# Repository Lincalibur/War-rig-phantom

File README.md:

<div align="center">

# War-rig-phantom
### *A Portable OPSEC/OSINT Recon Deck*

**A full ESP32-DIV multi-tool handheld (WiFi / BLE / 2.4 GHz / sub-GHz) plus standalone recon modules, with GPS-tagged logging**

**[Build page](https://lincalibur.github.io/War-rig-phantom/)**: boards, wiring diagram, parts checklist and build order

</div>

---

## Overview

**War-rig-phantom** is a portable wireless multi-tool and recon kit made of separate modules. Each module has its own screen and job:

- **`SPECTRE`** (role: `HUB`): the active handheld — an ESP32-WROOM-32U with a router antenna on U.FL, a **3.5" ILI9488 8-bit parallel TFT** and a NEO-7M GPS. It runs the ported **CyberDeck orchestrator** (a Ghost-ESP-style toolkit), driven from the `CONSOLE` phone app over BLE, on the ESP32's **built-in 2.4 GHz radio**: WiFi scan/deauth/evil-portal/packet-monitor/wardrive, BLE scan/spam, handshake → `.pcap` streamed to the phone, and HID. No radio shield, no buttons, no SD; one expansion SPI slot is reserved for a single future CC1101/NRF24.
- **`SENTINEL`** (roles: `WIFI-NODE` + `READOUT`): an ESP32-C3 WiFi/BLE sniffer streams over a one-way 19200 UART to an Arduino UNO with a 3.5" screen. It's the passive, always-on watcher — flags trackers, tails and attacks, and never transmits.
- **`BEACON`** (role: `STATUS`): a removable ESP32-C3 + OLED watch that logs GPS and WiFi scans to a phone.
- **`CONSOLE`:** the Android (Flutter) app that drives `SPECTRE` over BLE.

The modules share one 18650 pack and a 5 V boost module. Later, all the logs go to a laptop for analysis.

> **Scope & Ethics**
> `SPECTRE`'s orchestrator **includes active, transmitting tools** (WiFi deauth, beacon/probe/karma flood, evil portal, BLE spam, a best-effort BLE adv-flood "jammer", and HID) — all on the ESP32's built-in 2.4 GHz radio.
> - Use them **only** against hardware you own and control — the project's test laptop and spare router, on an isolated bench.
> - Never transmit against networks, devices or people you don't own. Deauth is illegal in most jurisdictions when aimed at others, and the radio interferes with anyone nearby.
> - The passive modules (`SENTINEL`, `BEACON`) only listen and log.
>
> This is an authorized-testing and learning platform. You are responsible for staying within the law.

## Architecture

```mermaid
flowchart TD
    subgraph SPECTREG["SPECTRE (HUB) · ported orchestrator firmware"]
      ESP["ESP32-WROOM-32U<br/>router antenna on U.FL<br/>built-in 2.4 GHz WiFi + BLE"]
      TFT["3.5 in ILI9488<br/>8-bit parallel, 320x480"]
      GPS["GPS · NEO-7M"]
      EXP["expansion SPI slot<br/>1 future radio, unused"]
      ESP -->|8-bit parallel| TFT
      GPS -->|UART2| ESP
      ESP -.->|SPI, future| EXP
    end
    CONSOLE["CONSOLE · Android app"] <-->|BLE| ESP
    ESP -.->|handshake .pcap over BLE| CONSOLE
    subgraph SENTG["SENTINEL (WIFI-NODE + READOUT) · passive, never TX"]
      WIFI["ESP32-C3<br/>promiscuous"] -->|UART 19200| READOUT["UNO + 3.5 in TFT"]
    end
    BEACON["BEACON (STATUS)<br/>C3 + OLED watch"] -->|CSV| PHONE["Android phone"]
    CONSOLE -.->|later| LAPTOP["Laptop analysis"]
    PHONE -.->|later| LAPTOP

    subgraph POWER["Power"]
      direction LR
      BAT["3x 18650 in parallel"] --> MSW["master switch"] --> BOOST["5V 2A charge/boost"] --> RAIL["5 V to every module"]
    end
```

SPECTRE wiring is documented in [`docs/hardware-layout.md`](docs/hardware-layout.md#spectre-pins) and [`hardware/spectre-pcb/PINOUT.md`](hardware/spectre-pcb/PINOUT.md). (The drawing [`docs/wiring.svg`](docs/wiring.svg) predates the 2026-11-15 pin remap and is stale.) Board names are defined in [`docs/hardware-layout.md`](docs/hardware-layout.md#module-names).

## Repository

| Path | What's in it |
|---|---|
| [`docs/OVERVIEW.md`](docs/OVERVIEW.md) | **Start here.** Goals, decisions, capabilities, status and next steps |
| [`docs/hardware-layout.md`](docs/hardware-layout.md) | The current build: board names, HUB pins, power, case |
| [`docs/case-planner.html`](docs/case-planner.html) | 3D case layout planner: size parts, drag them around the clamshell, check fit, export an OpenSCAD filler (live on the Pages site) |
| [`cad/wiring/`](cad/wiring/) | Script that draws the HUB wiring diagrams |
| [`docs/build-page.html`](docs/build-page.html) | Source of the build page (deployed by `.github/workflows/pages.yml`) |
| [`spectre/v1/`](spectre/v1/) | **SPECTRE firmware** — the orchestrator on one ESP32-WROOM-32U (see [`STATUS.md`](spectre/v1/STATUS.md)) |
| [`sentinel/v1/`](sentinel/v1/) | **SENTINEL firmware** — the passive watcher (ESP32-C3 + UNO pair) |
| [`hardware/spectre-pcb/`](hardware/spectre-pcb/) | SPECTRE custom carrier PCB (KiCad), on branch `spectre-pcb` |
| [`app/`](app/) | **CONSOLE** — the Android (Flutter) app that drives SPECTRE over BLE |
| [`docs/proto-readout-wiring.html`](docs/proto-readout-wiring.html) | SENTINEL C3 → UNO readout wiring |
| [`docs/BOARD-BLE-SCAN-ESP32-1732S019.md`](docs/BOARD-BLE-SCAN-ESP32-1732S019.md) | Spec for the `RELAY`/`BLE-SCAN` board (on hand, not in this build) |
| *(removed — see git tag `pre-cleanup-2026-11-20`)* | Shelved designs: single-PCB BOM, ESP32 hub-board page, KiCad CyberDeckv1, Pi 5 clamshell filler. Cut from the tree 2026-11-20, recoverable from the tag and git history |
| [`docs/debian-esp32-server-guide.md`](docs/debian-esp32-server-guide.md) | Remote compile/flash station over SSH (the server is being rebuilt) |

The `HUB` role is filled by **SPECTRE**, which runs the CyberDeck **orchestrator** firmware ported onto one ESP32-WROOM-32U ([`spectre/v1/`](spectre/v1/)) — **not** stock ESP32-DIV. cifertech's [ESP32-DIV](https://github.com/cifertech/ESP32-DIV) was only a reference example for "what's possible," not the codebase. The current, hardware-verified state (display = ILI9488 3.5" parallel, pinout, radios) lives in [`spectre/v1/STATUS.md`](spectre/v1/STATUS.md); the older stock-ESP32-DIV radio-shield spec in [`docs/hardware-layout.md`](docs/hardware-layout.md) predates the port and is still being reconciled (see the note at the top of that file).

The v1 build (ESP-NOW C3 nodes and an ESP32-1732S019 hub) was removed from the tree. Recover it with `git checkout v1-espnow-archive`.

## Status

| Area | State |
|---|---|
| HUB parts | 🟨 ordered from nde3d 2026-11-02, waiting for collection |
| HUB wiring and firmware | 🟨 wiring drawn from the firmware pins; prebuilt v1.7.0 ready to flash |
| WIFI-NODE + READOUT | ✅ working on the bench |
| STATUS watch | ✅ working |
| Power system | ⬜ ordered; bench test first |
| Case layout | ⬜ to be redrawn for these parts |
| Laptop analysis | ⬜ planned |

## License

See [LICENSE](LICENSE).

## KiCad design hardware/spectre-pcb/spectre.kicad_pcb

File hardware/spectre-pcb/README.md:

# SPECTRE HUB — KiCad carrier/baseboard PCB

A custom baseboard for the **SPECTRE HUB** so the ESP32, the 3.5" TFT shield, the GPS and
future expansion modules all **plug in / solder down** on one board instead of a wire nest.

This captures the **actual working firmware pinout** (`spectre/v1/User_Setup_SPECTRE.h` +
`spectre/v1/spectre/spectre.ino`) — ESP32-WROOM-32U + **ILI9488 8-bit PARALLEL** TFT +
NEO-7M GPS. It does **not** change the design; it just puts the existing wiring on a PCB you
can place and route.

Built and validated against **KiCad 10.0**. **ERC: 0 violations.** Netlist checked pin-by-pin.

## Files
| File | What it is |
|---|---|
| `generate_schematic.py` | The generator. Edit the pin maps and re-run (`python generate_schematic.py .`) to regenerate `spectre.kicad_sch`. |
| `spectre.kicad_sch` | The schematic: 23 symbols, all nets labelled, ready for PCB. |
| `spectre.kicad_pro` | Project file, with a **Power** netclass (1 mm tracks) on `+5V` / `+3V3` / `GND`. |
| `spectre.net` | Exported netlist (reference). |

## Board layout (done — placement + outline; routing is yours)
`spectre.kicad_pcb` already has the **outline and basic placement**. Open `spectre.kicad_pro`,
open the PCB Editor, and route — the full ratsnest is there. **`PINOUT.md`** is the human-readable
wiring map for every connector.

- **Portrait board, 75 × 150 mm** (screen is vertical → long board). 4× M3 corner holes, kept clear.
  Verified **0 footprint overlaps** (including no front/back pad collisions).
- **TFT on the FRONT:** the four UNO shield headers run vertically down both long edges
  (J3 power + J4 analog on the left, J6 + J5 digital on the right, ~48 mm apart to mate the shield).
- **ESP32 on the BACK:** J1/J2 (two 1×19 sockets) sit in the central gap, directly behind the screen.
- **Antennas at the TOP:** WiFi SMA (`ANT1`) top-left, NEO-7M GPS (`J7`) top-centre, power LED top-right.
- **Bottom:** expansion header `J8`, 5 V power in `J9`, decoupling/bulk caps.
- **Pin-name silk labels** next to every wired pad (net name, e.g. `CS`, `D0`, `3V3`, `SCK`): TFT/GPS/
  expansion/power on the **front**, ESP32 (J1/J2) on the **back** silk. Makes wiring/routing obvious.

Regenerate the PCB after editing placement: run
`"C:\Program Files\KiCad\10.0\bin\python.exe" generate_pcb.py` (edit the `PLACE` table first).
Note it rewrites `spectre.kicad_pcb`, so route on a copy or re-run before routing, not after.

### If you'd rather place it yourself from scratch
Delete `spectre.kicad_pcb`, open the project, PCB Editor → **Tools → Update PCB from Schematic**
(F8), then place and route. Power nets are already on 1 mm tracks via the Power netclass.

## What's on the board
| Ref | Part | Notes |
|---|---|---|
| J1 / J2 | **ESP32-WROOM-32U** DevKitC, two 1×19 sockets | The dev board sockets in. |
| J3 | **TFT** on one **Arduino-UNO-R3** footprint | Your mcufriend-style ILI9488 shield plugs straight on — exact Arduino geometry. |
| J7 | **NEO-7M GPS**, 1×5 | VCC/GND/TXD/RXD/PPS. |
| J8 | **Expansion**, 1×12 | VSPI bus + 4 input-only lines + power (see GPIO budget). |
| J9 | **5 V power in**, 1×2 | From the 1S 18650 + boost module. |
| R1 | 10k pulldown on IO12 (EXP_MOSI), **FIT** | Keeps the MTDI strap low at boot so a plugged-in expansion radio can't force 1.8 V flash selection. |
| R2 / D1 | Power LED | |
| C1–C8 | Decoupling | 100 nF at each VCC + 10 µF bulk on 5V/3V3. |

## ⚡ The 3.3 V logic rail (the white-screen fix, now designed in)
The shield's **3V3 pin powers the panel logic** and must be fed — supplying it is what finally
got the display working. On this board the ESP32 board's 3V3 regulator output (J1.1) runs to the
TFT power header (J3.4) and the expansion header. **Power the ESP32 from 5 V (VIN/J1.19)** so its
regulator produces that 3V3. Backlight is hardwired to VCC on the shield (no control pin — can't
be dimmed in firmware).

## ⚠️ GPIO budget — read before planning expansion
The 8-bit parallel TFT is GPIO-hungry: **13 pins** for the panel (CS/DC/RST/WR/RD + D0–D7) plus
**2** for GPS = 15 of the ESP32's usable I/O. What's left, and all that J8 exposes:

- **VSPI** — SCK=IO18, MOSI=IO23, MISO=IO19, one CS=IO5
- **4 input-only** lines — IO34, IO35, IO36, IO39 (good for IRQ / CC1101 GDO, not outputs)
- 3V3, 5V, GND

That is enough for **one SPI radio at a time** (a single CC1101 **or** one NRF24). The full
ESP32-DIV radio shield (**3× NRF24 + CC1101**) needs ~8 output control lines and **does not fit**
alongside the parallel TFT. If you want the full radio set later, the options are:
1. Fewer radios (one CC1101 or one NRF24 on J8) — fits now.
2. A second small MCU on the expansion SPI bus to own the radios (SENTINEL-style).
3. Switch SPECTRE's TFT to an **SPI** display — frees ~7 GPIOs, enough for the radios, but it's a
   different panel and a firmware change (the current parallel shield works today).

Decide this before committing a board outline, since it changes the connector count.

## ⚠️ Verify before you fab (modelled from docs, not the physical parts)
- **ESP32 pin order (most important).** J1/J2 use the canonical **DevKitC-V4** position order.
  Confirm against your actual WROOM-32U board; if a position differs, drag the net label (or edit
  the pin map in `generate_schematic.py` and re-run). IO6–IO11 are the internal flash pins — left
  unconnected on purpose; never route to them.
- **TFT shield mapping.** Now on the real **`Module:Arduino_UNO_R3`** footprint (exact UNO geometry,
  so the shield mates), wired to the **mcufriend standard**: LCD_D0/D1 on Arduino D8/D9, LCD_D2–D7 on
  D2–D7, LCD_RD/WR/RS/CS/RST on A0–A4. Confirm your shield matches (most red 3.5" parallel shields do).
  The TFT shield mounts on the **front**; the ESP32 is on the **back**, so they don't collide.
- **GPS VCC.** On +5V (the NEO-7M module regulates). If it won't get a fix on 5 V, move J7.1 to
  +3V3. **Unplug GPS TXD while flashing** only matters on boards that share USB-serial pins — here
  GPS is on IO15/IO2 (UART2 remapped), clear of the USB pins, so flashing is fine with it attached.
- **Strapping pins.** After the 2026-11-15 remap the TFT bus is off the fragile straps. Remaining
  strap-pin uses: IO12 = `EXP_MOSI` (fit R1 10k pulldown — boot insurance), IO2/IO15 = GPS UART
  (ESP32-driven TX / idle-high RX, both safe), IO5 = `TFT_D4` (data line, boot glitch harmless),
  IO0 = BOOT button. `EXP_CS0` on IO4 wants a 10k pull-up so it isn't asserted at boot.

## Design notes
- One parallel bus for the display (`TFT_D0..D7` + control); a separate SPI bus for expansion.
- GPS on UART2 (IO15 RX ← GPS TXD, IO2 TX → GPS RXD), independent of the 2.4 GHz radio.
- Keep decoupling caps at the module pins when you place. Add a separate 3V3 LDO (not placed) if a
  future expansion radio browns out the dev-board regulator.

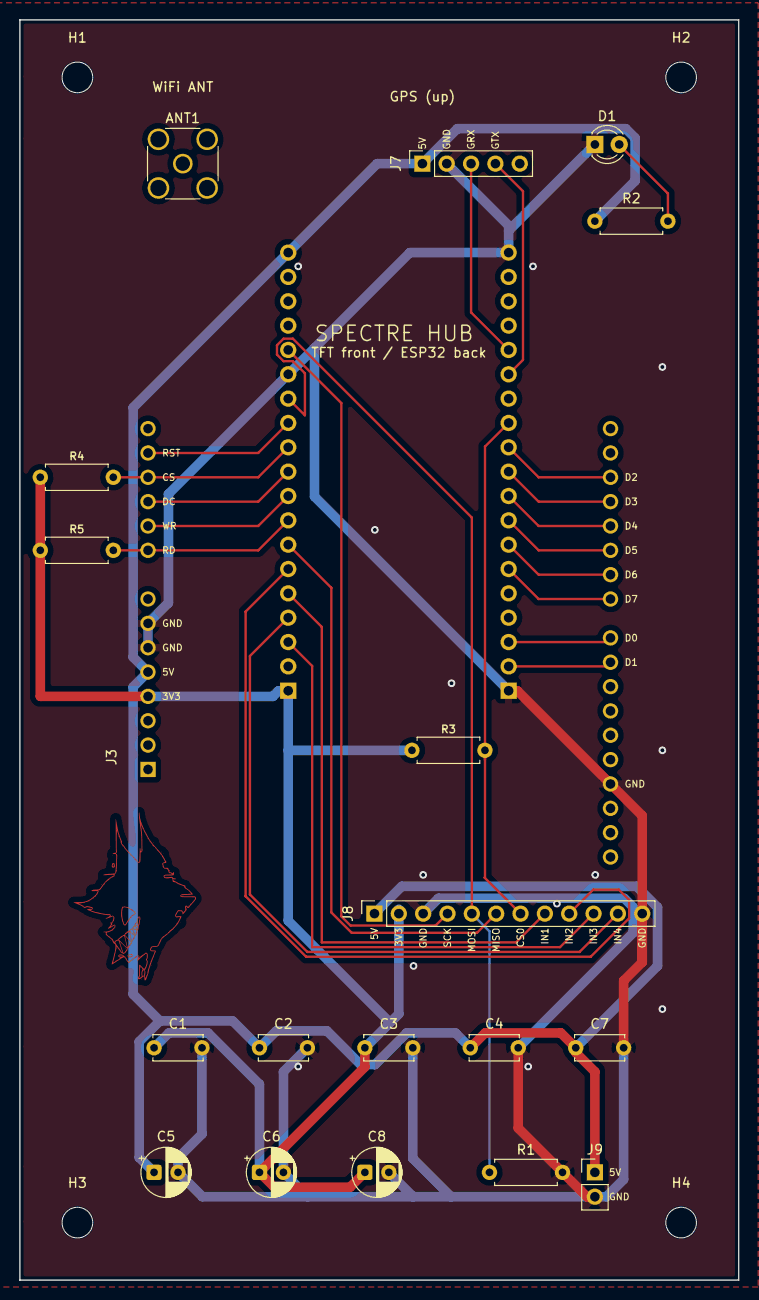
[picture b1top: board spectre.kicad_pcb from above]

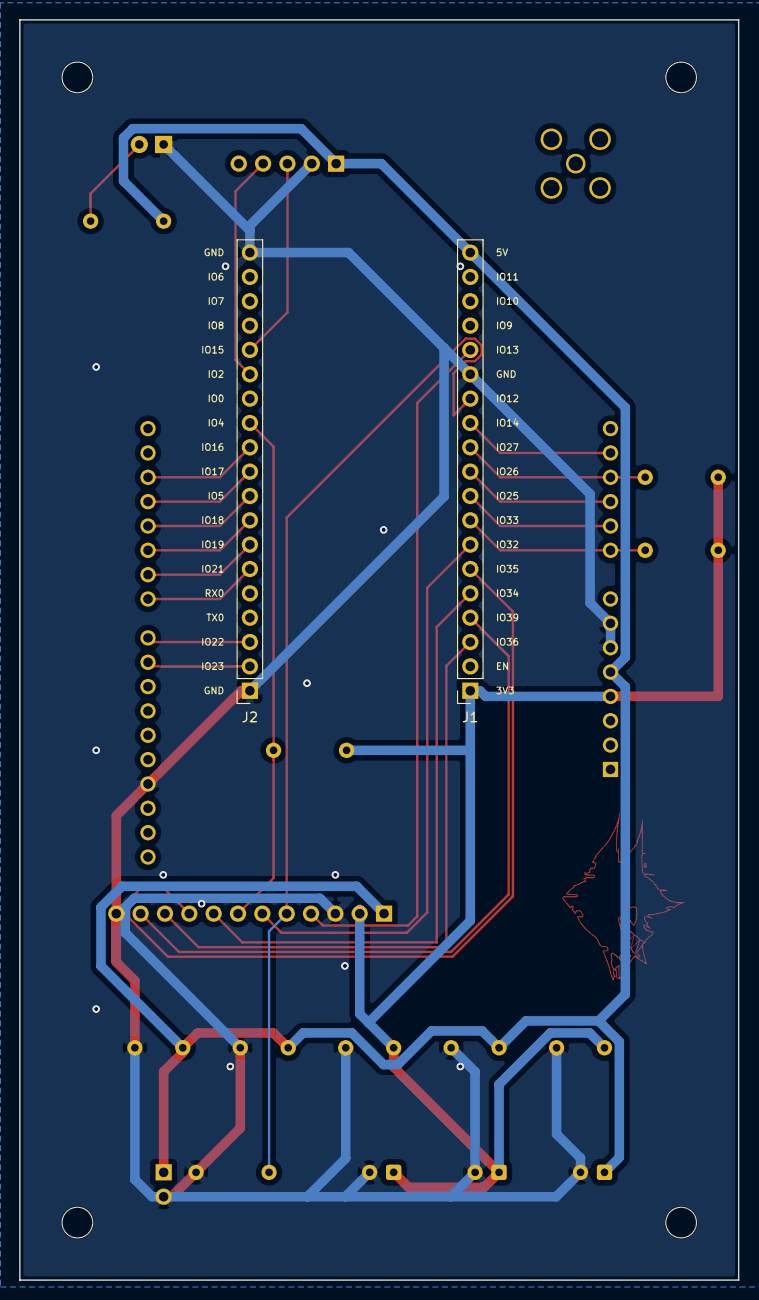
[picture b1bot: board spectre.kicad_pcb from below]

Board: 2 copper layers, 75.0 x 131.5 mm, 25 parts (2 on the bottom side), 27 nets.

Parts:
ANT1: SMA_Amphenol_132134_Vertical
C1, C2, C3, C4, C7: C_Disc_D5.0mm_W2.5mm_P5.00mm
C5, C6, C8: CP_Radial_D5.0mm_P2.50mm
D1: LED_D3.0mm
H1, H2, H3, H4: MountingHole_3.2mm_M3
J1, J2: PinSocket_1x19_P2.54mm_Vertical
J3: Arduino_UNO_R3
J7: PinSocket_1x05_P2.54mm_Vertical
J8: PinSocket_1x12_P2.54mm_Vertical
J9: PinHeader_1x02_P2.54mm_Vertical
R1, R2: R_Axial_DIN0207_L6.3mm_D2.5mm_P7.62mm_Horizontal
R3, R4, R5: 10k; R_Axial_DIN0207_L6.3mm_D2.5mm_P7.62mm_Horizontal

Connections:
+3V3: C1.1, C3.1, C6.1, C8.1, J1.1, J3.4, J8.2, R3.1, R4.1, R5.1
+5V: C2.1, C4.1, C5.1, C7.1, J1.19, J3.5, J7.1, J8.1, J9.1, R2.1
EXP_CS0: J2.12, J8.7, R3.2
EXP_IN1: J1.5, J8.8
EXP_IN2: J1.6, J8.9
EXP_IN3: J1.3, J8.10
EXP_IN4: J1.4, J8.11
EXP_MISO: J1.7, J8.6
EXP_MOSI: J1.13, J8.5, R1.1
EXP_SCK: J1.15, J8.4
GND: C1.2, C2.2, C3.2, C4.2, C5.2, C6.2, C7.2, C8.2, D1.1, J1.14, J2.1, J2.19, J3.6, J3.7, J3.29, J7.2, J8.3, J8.12, J9.2, R1.2
GPS_RX: J2.15, J7.3
GPS_TX: J2.14, J7.4
LED_A: D1.2, R2.2
TFT_CS: J1.11, J3.12, R4.2
TFT_D0: J2.3, J3.23
TFT_D1: J2.2, J3.24
TFT_D2: J2.11, J3.17
TFT_D3: J2.10, J3.18
TFT_D4: J2.9, J3.19
TFT_D5: J2.8, J3.20
TFT_D6: J2.7, J3.21
TFT_D7: J2.6, J3.22
TFT_DC: J1.10, J3.11
TFT_RD: J1.8, J3.9, R5.2
TFT_RST: J1.12, J3.13
TFT_WR: J1.9, J3.10

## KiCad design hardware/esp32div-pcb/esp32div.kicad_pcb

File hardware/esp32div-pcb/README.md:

# ESP32-DIV HUB — KiCad carrier PCB (schematic pre-built)

A starting point for routing a custom carrier/shield PCB for the **HUB** board
(the ESP32-DIV handheld in [`../../docs/hardware-layout.md`](../../docs/hardware-layout.md)).
Every plug-in module is a female-header footprint; the ESP32 dev board and all
modules socket in. This does **not** change the design — it just captures the
existing HUB pinout in KiCad so you can place and route.

Built and validated against **KiCad 10.0.6**. Netlist checked pin-by-pin; ERC
clean except one benign warning (see below).

## Files
| File | What it is |
|---|---|
| `esp32div.kicad_sch` | The schematic: 39 symbols, all nets labelled, ready for PCB. |
| `esp32div.kicad_pro` | Project file. Includes a **Power** netclass (1 mm tracks) auto-applied to `+5V`, `+3V3`, `GND`, `VBAT`, `VBOOST`. |
| `generate_schematic.py` | The generator. Edit the pin maps and re-run (`python generate_schematic.py .`) to regenerate the schematic. |

## Go straight to routing
1. Open `esp32div.kicad_pro` in KiCad.
2. Open the **PCB Editor** (it creates `esp32div.kicad_pcb`).
3. **Tools → Update PCB from Schematic** (F8) → *Update*. All 39 footprints drop
   in with the full ratsnest.
4. Draw a board outline on Edge.Cuts, then place and route. The power nets are
   already on 1 mm tracks via the Power netclass.

## The one ERC warning
`lib_symbol_mismatch` on `PCF8574T` — the PCF8574 is a *derived* library symbol,
so the cached copy isn't byte-identical to the library. It's cosmetic and does
**not** affect the netlist or PCB. To clear it: **Tools → Update Symbols from
Library** in the schematic editor.

## ⚠️ Verify before you fab (modelled from docs, not physical parts)
- **ESP32 pin order (most important).** `J1`/`J2` are modelled as two 1×19
  headers using the standard **38-pin DevKitC-V4** order. Confirm against your
  actual WROOM-32U board when it arrives. If a pin differs, just drag the net
  label to the correct pin (or edit the pin map in `generate_schematic.py` and
  re-run). The board can't be finalised until the dev-board variant is confirmed
  (see the open question in `hardware-layout.md`).
- **TFT header (`J3`).** Modelled as one 18-way header with the full
  TFT+touch+SD signal set. Match pin order/count to your physical 2.4" module.
- **CC1101 (`J8`) and NRF24 (`J5–J7`) pin order.** Vendor-dependent; check the
  silkscreen on your modules. NRF24 uses a 2×4 socket footprint.
- **VCC rails.** TFT and GPS VCC are on `+5V` per the docs (both have on-board
  regulators). Confirm your modules accept 5 V. PCF8574, NRF24, CC1101 are on
  `+3V3`.

## Design notes carried over from the docs
- Two SPI buses: display pixels on `TFT_*` (IO14/13/12), everything else (touch,
  SD, 3× NRF24, CC1101) on the shared `SH_*` bus (IO18/23/19).
- Intentionally **shared** control nets (cifertech firmware time-shares them):
  `SD_CS_NRF1_CSN` (IO5), `NRF2_CE_CC_GDO0` (IO26), `NRF2_CSN_CC_CS` (IO27),
  `NRF3_CE_CC_GDO2` (IO16). These fan out to several module pins by design.
- Decoupling: 100 nF at every module VCC; extra 10 µF at each NRF24, the CC1101
  and the GPS. Keep them at the pins when you place.
- Consider the optional separate 3V3 LDO for the radios (not placed) if the dev
  board's regulator browns out under 3× NRF24 + CC1101.

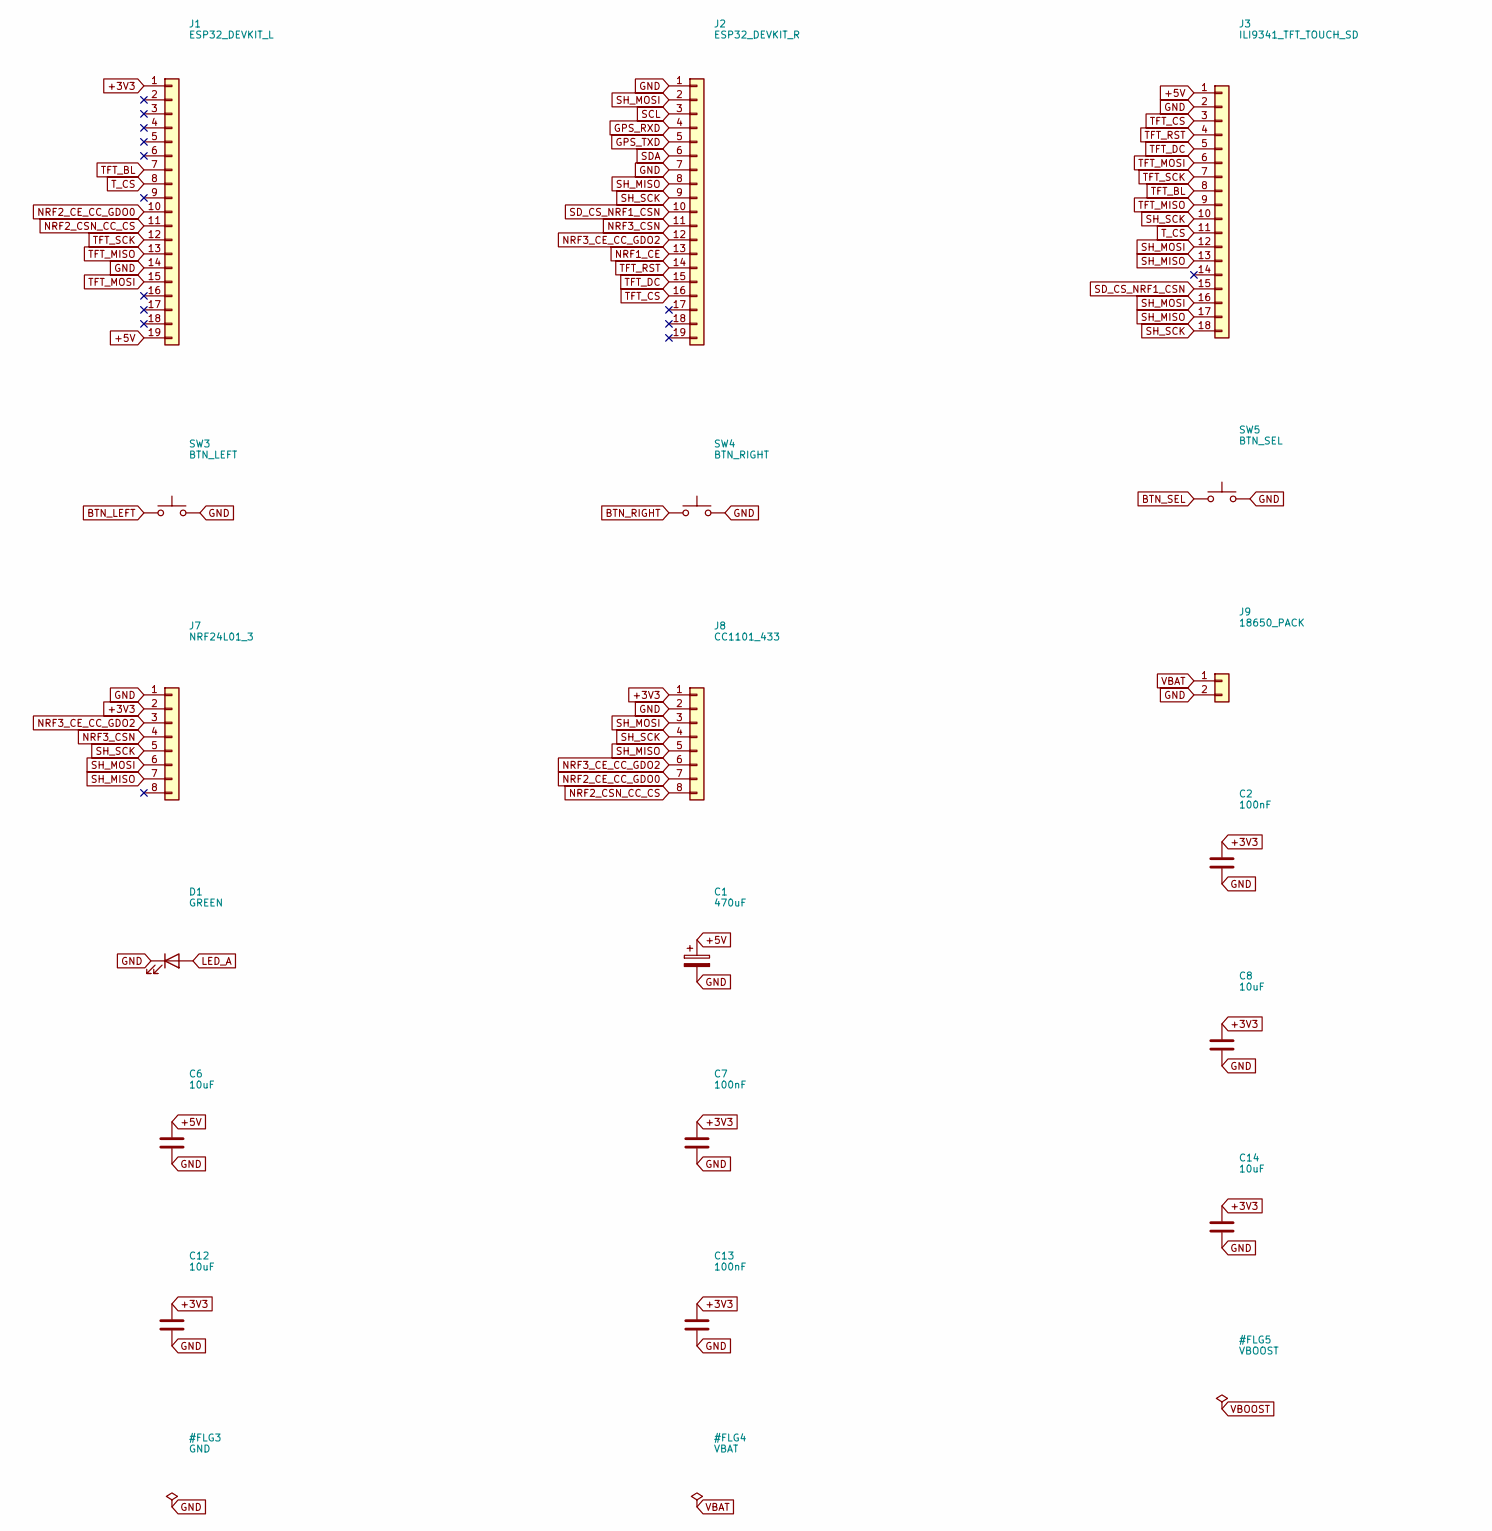
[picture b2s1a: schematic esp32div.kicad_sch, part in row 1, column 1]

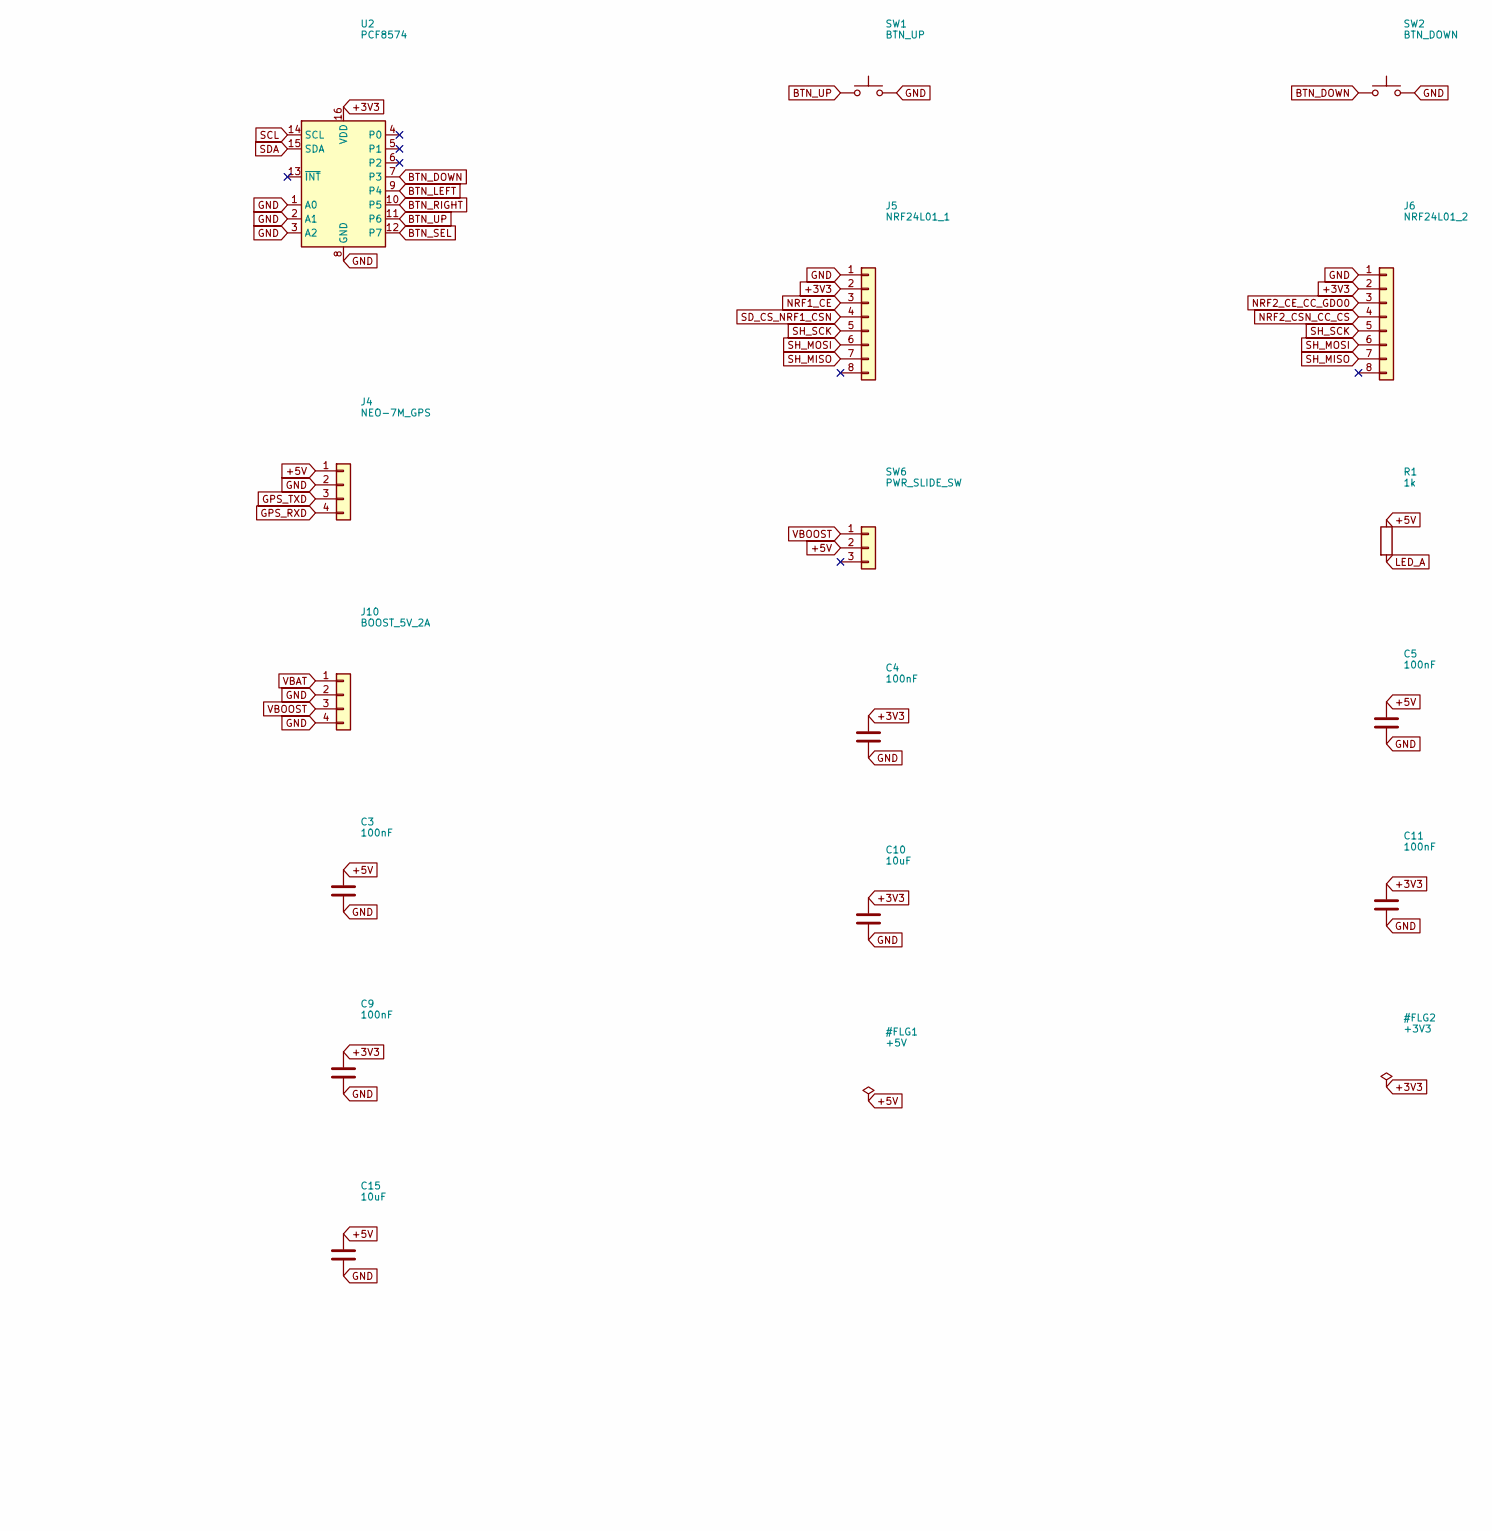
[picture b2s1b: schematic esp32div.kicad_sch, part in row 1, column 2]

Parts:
C1: 470uF; CP_Radial_D8.0mm_P3.50mm
C2, C3, C4, C5, C7, C9, C11, C13: 100nF; C_Disc_D5.0mm_W2.5mm_P5.00mm
C6, C8, C10, C12, C14, C15: 10uF; CP_Radial_D5.0mm_P2.50mm
D1: GREEN; LED_D3.0mm
J1: ESP32_DEVKIT_L; PinSocket_1x19_P2.54mm_Vertical
J2: ESP32_DEVKIT_R; PinSocket_1x19_P2.54mm_Vertical
J3: ILI9341_TFT_TOUCH_SD; PinSocket_1x18_P2.54mm_Vertical
J4: NEO-7M_GPS; PinSocket_1x04_P2.54mm_Vertical
J5: NRF24L01_1; PinSocket_2x04_P2.54mm_Vertical
J6: NRF24L01_2; PinSocket_2x04_P2.54mm_Vertical
J7: NRF24L01_3; PinSocket_2x04_P2.54mm_Vertical
J8: CC1101_433; PinSocket_1x08_P2.54mm_Vertical
J9: 18650_PACK; PinHeader_1x02_P2.54mm_Vertical
J10: BOOST_5V_2A; PinHeader_1x04_P2.54mm_Vertical
R1: 1k; R_Axial_DIN0207_L6.3mm_D2.5mm_P7.62mm_Horizontal
SW1: BTN_UP; SW_PUSH_6mm
SW2: BTN_DOWN; SW_PUSH_6mm
SW3: BTN_LEFT; SW_PUSH_6mm
SW4: BTN_RIGHT; SW_PUSH_6mm
SW5: BTN_SEL; SW_PUSH_6mm
SW6: PWR_SLIDE_SW; PinHeader_1x03_P2.54mm_Vertical
U2: PCF8574; SOIC-16_3.9x9.9mm_P1.27mm

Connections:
+3V3: C2.1, C4.1, C7.1, C8.1, C9.1, C10.1, C11.1, C12.1, C13.1, C14.1, J1.1, J5.2, J6.2, J7.2, J8.1, U2.16 (VDD)
+5V: C1.1, C3.1, C5.1, C6.1, C15.1, J1.19, J3.1, J4.1, R1.1, SW6.2
BTN_DOWN: SW2.1, U2.7 (P3)
BTN_LEFT: SW3.1, U2.9 (P4)
BTN_RIGHT: SW4.1, U2.10 (P5)
BTN_SEL: SW5.1, U2.12 (P7)
BTN_UP: SW1.1, U2.11 (P6)
GND: C1.2, C2.2, C3.2, C4.2, C5.2, C6.2, C7.2, C8.2, C9.2, C10.2, C11.2, C12.2, C13.2, C14.2, C15.2, D1.1 (K), J1.14, J2.1, J2.7, J3.2, J4.2, J5.1, J6.1, J7.1, J8.2, J9.2, J10.2, J10.4, SW1.2, SW2.2, SW3.2, SW4.2, SW5.2, U2.1 (A0), U2.2 (A1), U2.3 (A2), U2.8 (GND)
GPS_RXD: J2.4, J4.4
GPS_TXD: J2.5, J4.3
LED_A: D1.2 (A), R1.2
NRF1_CE: J2.13, J5.3
NRF2_CE_CC_GDO0: J1.10, J6.3, J8.7
NRF2_CSN_CC_CS: J1.11, J6.4, J8.8
NRF3_CE_CC_GDO2: J2.12, J7.3, J8.6
NRF3_CSN: J2.11, J7.4
SCL: J2.3, U2.14 (SCL)
SDA: J2.6, U2.15 (SDA)
SD_CS_NRF1_CSN: J2.10, J3.15, J5.4
SH_MISO: J2.8, J3.13, J3.17, J5.7, J6.7, J7.7, J8.5
SH_MOSI: J2.2, J3.12, J3.16, J5.6, J6.6, J7.6, J8.3
SH_SCK: J2.9, J3.10, J3.18, J5.5, J6.5, J7.5, J8.4
TFT_BL: J1.7, J3.8
TFT_CS: J2.16, J3.3
TFT_DC: J2.15, J3.5
TFT_MISO: J1.13, J3.9
TFT_MOSI: J1.15, J3.6
TFT_RST: J2.14, J3.4
TFT_SCK: J1.12, J3.7
T_CS: J1.8, J3.11
VBAT: J9.1, J10.1
VBOOST: J10.3, SW6.1

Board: 2 copper layers, 34 parts (28 on the bottom side), 32 nets, no tracks yet.

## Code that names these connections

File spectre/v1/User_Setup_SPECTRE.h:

// TFT_eSPI User_Setup for the SPECTRE HUB — 3.5" ILI9486 parallel (mcufriend-style) UNO shield.
//
// Deploy: copy this over  <Arduino>/libraries/TFT_eSPI/User_Setup.h  (User_Setup_Select.h already
// includes <User_Setup.h> by default), then rebuild spectre/v1/spectre.
//
// The shield is 8-bit PARALLEL. All 8 data pins must be on GPIOs < 32 so one register write drives
// the bus. Pins are the SPECTRE wiring (see docs/hardware-layout.md).
//
// Controller: this red 3.5" shield is almost always ILI9486 (320x480). If the screen stays white or
// shows wrong colours, try the alternates below one at a time (ILI9488, then HX8357 / ILI9481).

#define USER_SETUP_INFO "SPECTRE Parallel ILI9486"

// ---- Driver (uncomment ONE) ----
// Confirmed by the diag read on 2026-11-14: RDID 0xD3 -> 94 88 = ILI9488.
//#define ILI9486_DRIVER
#define ILI9488_DRIVER
//#define HX8357D_DRIVER
//#define ILI9481_DRIVER
//#define ILI9341_DRIVER     // 2.4"/2.8" panels only

// ---- 8-bit parallel bus on the ESP32 ----
#define TFT_PARALLEL_8_BIT

#define TFT_WIDTH  320
#define TFT_HEIGHT 480

// Control lines  (optimized SPECTRE-carrier mapping, 2026-11-15)
#define TFT_CS   27   // LCD_CS (library pulls permanently low)
#define TFT_DC   26   // LCD_RS / DC   (bank<32)
#define TFT_RST  14   // LCD_RST
#define TFT_WR   25   // LCD_WR write strobe (bank<32 -> faster pulsing)
#define TFT_RD   33   // LCD_RD read strobe (rarely toggles; upper-bank pin is fine)

// Data bus (all < 32 so one register write drives the byte; order is free - LUT driven)
#define TFT_D0   22
#define TFT_D1   23
#define TFT_D2   16
#define TFT_D3   17
#define TFT_D4    5
#define TFT_D5   18
#define TFT_D6   19
#define TFT_D7   21

// Backlight is hardwired to VCC on this shield — no TFT_BL.

// ---- Fonts ----
#define LOAD_GLCD
#define LOAD_FONT2
#define LOAD_FONT4
#define LOAD_FONT6
#define LOAD_FONT7
#define LOAD_FONT8
#define LOAD_GFXFF
#define SMOOTH_FONT

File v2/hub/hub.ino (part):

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// Pins
// ---------------------------------------------------------------------------------------
static const int PIN_SCLK = 12, PIN_MOSI = 11, PIN_MISO = 13;
static const int PIN_TFT_CS = 10, PIN_TFT_DC = 9, PIN_TFT_RST = 8, PIN_TFT_BL = 7;
static const int PIN_SD_CS = 14;
static const int PIN_CC1101_CS = 15;   // reserved; held high so it doesn't fight the shared bus
static const int PIN_WIFI_RX = 4, PIN_WIFI_TX = 5;   // UART1 <-> WiFi node
static const int PIN_BLE_RX  = 1, PIN_BLE_TX  = 2;   // UART2 <-> BLE node
static const int PIN_BTN_UP = 38, PIN_BTN_DOWN = 39, PIN_BTN_LEFT = 40, PIN_BTN_RIGHT = 41, PIN_BTN_SEL = 42;
static const int PIN_BAT_LOW = 47;     // PowerBoost LBO, active low

// ---------------------------------------------------------------------------------------
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// Display
// ---------------------------------------------------------------------------------------
static SPIClass hubSpi(FSPI);
static Adafruit_ILI9341 tft(&hubSpi, PIN_TFT_DC, PIN_TFT_CS, PIN_TFT_RST);

static const uint16_t C_BG = 0x0000, C_FG = 0xFFFF, C_GRAY = 0x8410, C_GREEN = 0x07E0, C_RED = 0xF800,
                      C_YELLOW = 0xFFE0, C_CYAN = 0x07FF, C_ORANGE = 0xFD20, C_HEAD = 0x0010;
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// ---------------------------------------------------------------------------------------
struct Button { int pin; bool repeat; uint32_t nextMs; bool wasDown; };
static Button buttons[] = {
  {PIN_BTN_UP, true, 0, false}, {PIN_BTN_DOWN, true, 0, false}, {PIN_BTN_LEFT, false, 0, false},
  {PIN_BTN_RIGHT, false, 0, false}, {PIN_BTN_SEL, false, 0, false},
};

static void onButton(int pin) {
  if (pin == PIN_BTN_UP) scroll -= 1;
  else if (pin == PIN_BTN_DOWN) scroll += 1;
  else if (pin == PIN_BTN_LEFT) { changePage(-1); return; }
  else if (pin == PIN_BTN_RIGHT) { changePage(+1); return; }
  else if (pin == PIN_BTN_SEL) sortMode = (sortMode + 1) % SORT_COUNT;
  if (scroll < 0) scroll = 0;
  dirty = true;
}
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  Serial.begin(115200);

  // Deselect every SPI device before the bus is used.
  for (int cs : {PIN_TFT_CS, PIN_SD_CS, PIN_CC1101_CS}) { pinMode(cs, OUTPUT); digitalWrite(cs, HIGH); }
  pinMode(PIN_TFT_BL, OUTPUT); digitalWrite(PIN_TFT_BL, HIGH);
  for (Button& b : buttons) pinMode(b.pin, INPUT_PULLUP);
  pinMode(PIN_BAT_LOW, INPUT_PULLUP);

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
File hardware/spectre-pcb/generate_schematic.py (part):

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 "5":"EXP_IN1",   # IO34  input-only
 "6":"EXP_IN2",   # IO35  input-only
 "7":"EXP_MISO",  # IO32  (full I/O; used as SPI MISO input - expansion)
 "8":"TFT_RD",    # IO33  LCD read strobe (rarely toggles; upper-bank pin is fine here)
 "9":"TFT_WR",    # IO25  LCD write strobe (bank<32 -> fast pulsing)
 "10":"TFT_DC",   # IO26
 "11":"TFT_CS",   # IO27
 "12":"TFT_RST",  # IO14
 "13":"EXP_MOSI", # IO12  (STRAPPING MTDI - must be LOW at boot; FIT R1 pulldown as insurance)
 "14":"GND",      # GND
 "15":"EXP_SCK",  # IO13
 "16":NC,         # IO9   flash - do not use
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 "6":"TFT_D7",    # IO21
 "7":"TFT_D6",    # IO19
 "8":"TFT_D5",    # IO18
 "9":"TFT_D4",    # IO5   (strapping pin, fine as a data line - a boot glitch here is harmless)
 "10":"TFT_D3",   # IO17
 "11":"TFT_D2",   # IO16
 "12":"EXP_CS0",  # IO4   (expansion chip-select; add 10k pull-up when finalising)
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 "25":NC,"26":NC,"27":NC,"28":NC,"30":NC,"31":NC,"32":NC})

# =======================================================================================
# NEO-7M GPS (UART2). Header labels VCC/GND/TXD/RXD. GPS TXD -> ESP32 RX2 (net GPS_RX);
# GPS RXD <- ESP32 TX2 (net GPS_TX). VCC on +5V (module regulates); see README for 3V3 option.
# =======================================================================================
add("J7", C+"Conn_01x05", "NEO-7M_GPS", PH+"PinSocket_1x05_P2.54mm_Vertical", {
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    {"1":"+5V","2":"LED_A"})
add("D1", "Device:LED", "GREEN", "LED_THT:LED_D3.0mm", {"K":"GND","A":"LED_A"}, byname=True)

# Pulldown on IO12 (now EXP_MOSI) strapping pin - FIT (not DNP) as boot insurance: keeps IO12
# low at reset so a connected expansion radio can't force 1.8V flash selection (-> no boot).
add("R1", "Device:R", "10k", "Resistor_THT:R_Axial_DIN0207_L6.3mm_D2.5mm_P7.62mm_Horizontal",
    {"1":"EXP_MOSI","2":"GND"})
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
